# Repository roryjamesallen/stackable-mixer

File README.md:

# stackable-mixer
A versatile, affordable, free hardware, stereo mixer for Eurorack

Each input channel has either mono or stereo inputs, a balance control, a mute switch, and a volume control.
The output stage has a stereo TRS (headphone) output, but patching into the right input will break the normalling, allowing you to output stereo over two mono cables.
The output also has a mute switch and volume control, so you can easily mute your system or adjust the master volume depending on where your output is going.
  
Each input channel is passive, so can be made very affordably, although ±12V and Earth are available from the bus which carries the stereo signals, so future/user-developed input stages could be active, for example an input stage with an active EQ.
  
There is also of course the potential for alternative output stages, such as balanced 6.35mm or separate output and monitor outputs for headphone monitoring during a live set.

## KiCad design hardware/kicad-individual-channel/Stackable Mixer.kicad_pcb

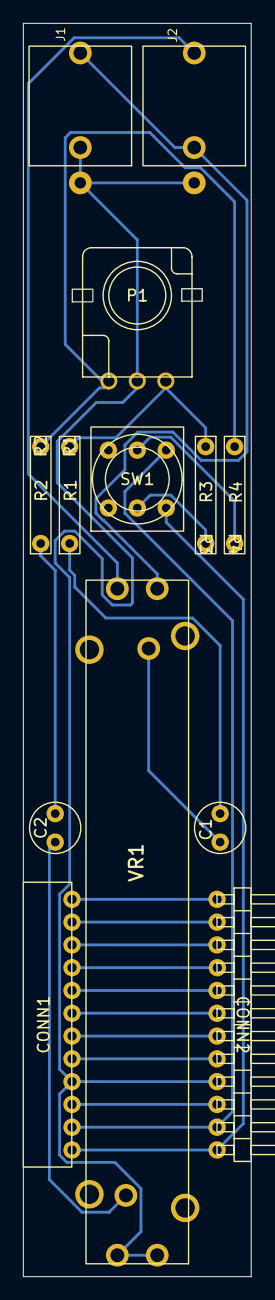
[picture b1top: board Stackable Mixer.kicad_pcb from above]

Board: 2 copper layers, 20.0 x 110.0 mm, 13 parts (0 on the bottom side), 22 nets.

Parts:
C1, C2: 100nF; Capacitor Small Non-Polarised
CONN1: Header_2.0mm_Right_Angle_Female; Header 01x12 2.0mm Right Angle Female
CONN2: Header_2.0mm_Right_Angle_Male; Header 01x12 2.0mm Right Angle Male
J1: L/Mono; Thonkiconn Mono Jack
J2: R; Thonkiconn Mono Jack
P1: Potentiometer_9mm_Vertical_Linear; Potentiometer 9mm Vertical Linear
R1, R2: 100k; Resistor 0.25W Through-Hole
R3, R4: 4.7k; Resistor 0.25W Through-Hole
SW1: SW_DPDT_x2; Sub-Miniature Toggle Switch DPDT
VR1: Potentiometer_45mm_Slide_Audio_Dual; Potentiometer 45mm Slide Audio

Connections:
/+12V: CONN1.5, CONN2.8
/-12V: CONN1.3, CONN2.10
/LEFT BUS: CONN1.1, CONN2.12, SW1.1 (A)
/LEFT SIGNAL: R3.2, SW1.2 (B)
/RIGHT BUS: CONN1.2, CONN2.11, SW1.4 (A)
/RIGHT SIGNAL: R4.2, SW1.5 (B)
Earth: CONN1.4, CONN2.9, J1.1 (E), J1.2 (S), J2.1 (E), P1.2, VR1.1, VR1.4
unnamed: C1.1, VR1.5
unnamed: C1.2, R1.1
unnamed: C2.1, VR1.2
unnamed: C2.2, R2.1
unnamed: CONN1.6, CONN2.7
unnamed: CONN1.7, CONN2.6
unnamed: CONN1.8, CONN2.5
unnamed: CONN1.9, CONN2.4
unnamed: CONN1.10, CONN2.3
unnamed: CONN1.11, CONN2.2
unnamed: CONN1.12, CONN2.1
unnamed: J1.3 (T), J2.2 (S), VR1.6
unnamed: J2.3 (T), VR1.3
unnamed: P1.1, R2.2, R4.1
unnamed: P1.3, R1.2, R3.1

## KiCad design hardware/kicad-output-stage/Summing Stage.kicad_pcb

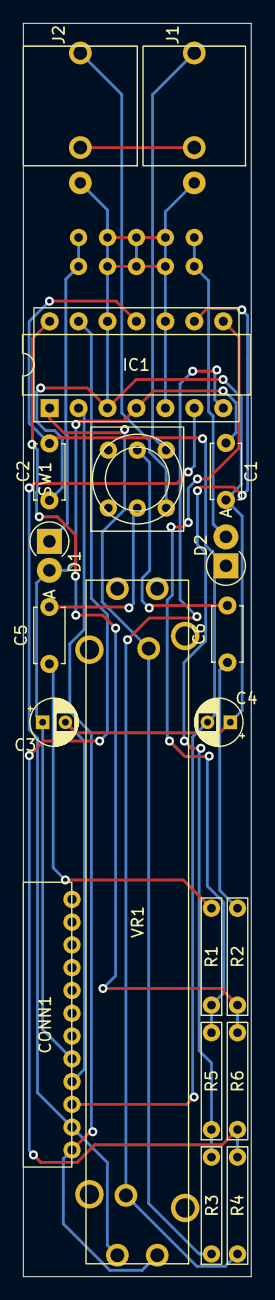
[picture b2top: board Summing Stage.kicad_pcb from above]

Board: 2 copper layers, 20.0 x 110.0 mm, 21 parts (1 on the bottom side), 18 nets.

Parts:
C1, C2, C5, C6: 100n; C_Disc_D4.7mm_W2.5mm_P5.00mm
C3, C4: 10u; CP_Radial_D4.0mm_P2.00mm
CONN1: Header_2.0mm_Right_Angle_Female; Header 01x12 2.0mm Right Angle Female
D1, D2: DIODE; D_DO-41_SOD81_P2.54mm_Vertical_AnodeUp
IC1: TL074; DIP-14 IC Socket
J1: Thonkiconn_Mono_Jack; Thonkiconn Mono Jack
J2: AudioJack3; Thonkiconn Stereo Jack
PowerHeader1: Conn_02x05_Counter_Clockwise; Eurorack Power Header
R1, R2: 1k; Resistor 0.25W Through-Hole
R3, R4, R5, R6: 4.7k; Resistor 0.25W Through-Hole
SW1: SW_DPDT_x2; Sub-Miniature Toggle Switch DPDT
VR1: Potentiometer_45mm_Slide_Audio_Dual; Potentiometer 45mm Slide Audio

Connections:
+12V: C1.1, C3.1, CONN1.5, D1.2 (K), IC1.4 (V+)
-12V: C2.2, C4.2, CONN1.3, D2.1 (A), IC1.11 (V-)
Earth: C1.2, C2.1, C3.2, C4.1, CONN1.4, IC1.3 (+), IC1.5 (+), IC1.10 (+), IC1.12 (+), J1.1 (E), PowerHeader1.3, PowerHeader1.4, PowerHeader1.5, PowerHeader1.6, PowerHeader1.7, PowerHeader1.8
unnamed: C5.1, R1.2
unnamed: C5.2, SW1.2 (B)
unnamed: C6.1, R2.2
unnamed: C6.2, SW1.5 (B)
unnamed: CONN1.1, IC1.2 (-), VR1.4
unnamed: CONN1.2, IC1.6 (-), VR1.1
unnamed: D1.1 (A), PowerHeader1.9, PowerHeader1.10
unnamed: D2.2 (K), PowerHeader1.1, PowerHeader1.2
unnamed: IC1.1, R3.1, VR1.5
unnamed: IC1.7, R4.1, VR1.2
unnamed: IC1.8, R1.1, R5.2
unnamed: IC1.9 (-), R3.2, R5.1
unnamed: IC1.13 (-), R4.2, R6.1
unnamed: IC1.14, R2.1, R6.2
R OUT: J1.3 (T), SW1.4 (A)

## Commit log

2022-03-21 Change extensions for kicad 6
2022-03-21 Add render and 3d model
2022-04-05 Move links to extras
2022-04-07 Add image
2022-04-07 make links hyperlinks

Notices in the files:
hardware/kicad-individual-channel/Stackable Mixer.kicad_pcb:
CERN OHL-S v2
